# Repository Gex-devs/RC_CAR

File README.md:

# RC_CAR

ESP32 based RC Car using Xbox One Controller

## Components

## Software 

## Tools

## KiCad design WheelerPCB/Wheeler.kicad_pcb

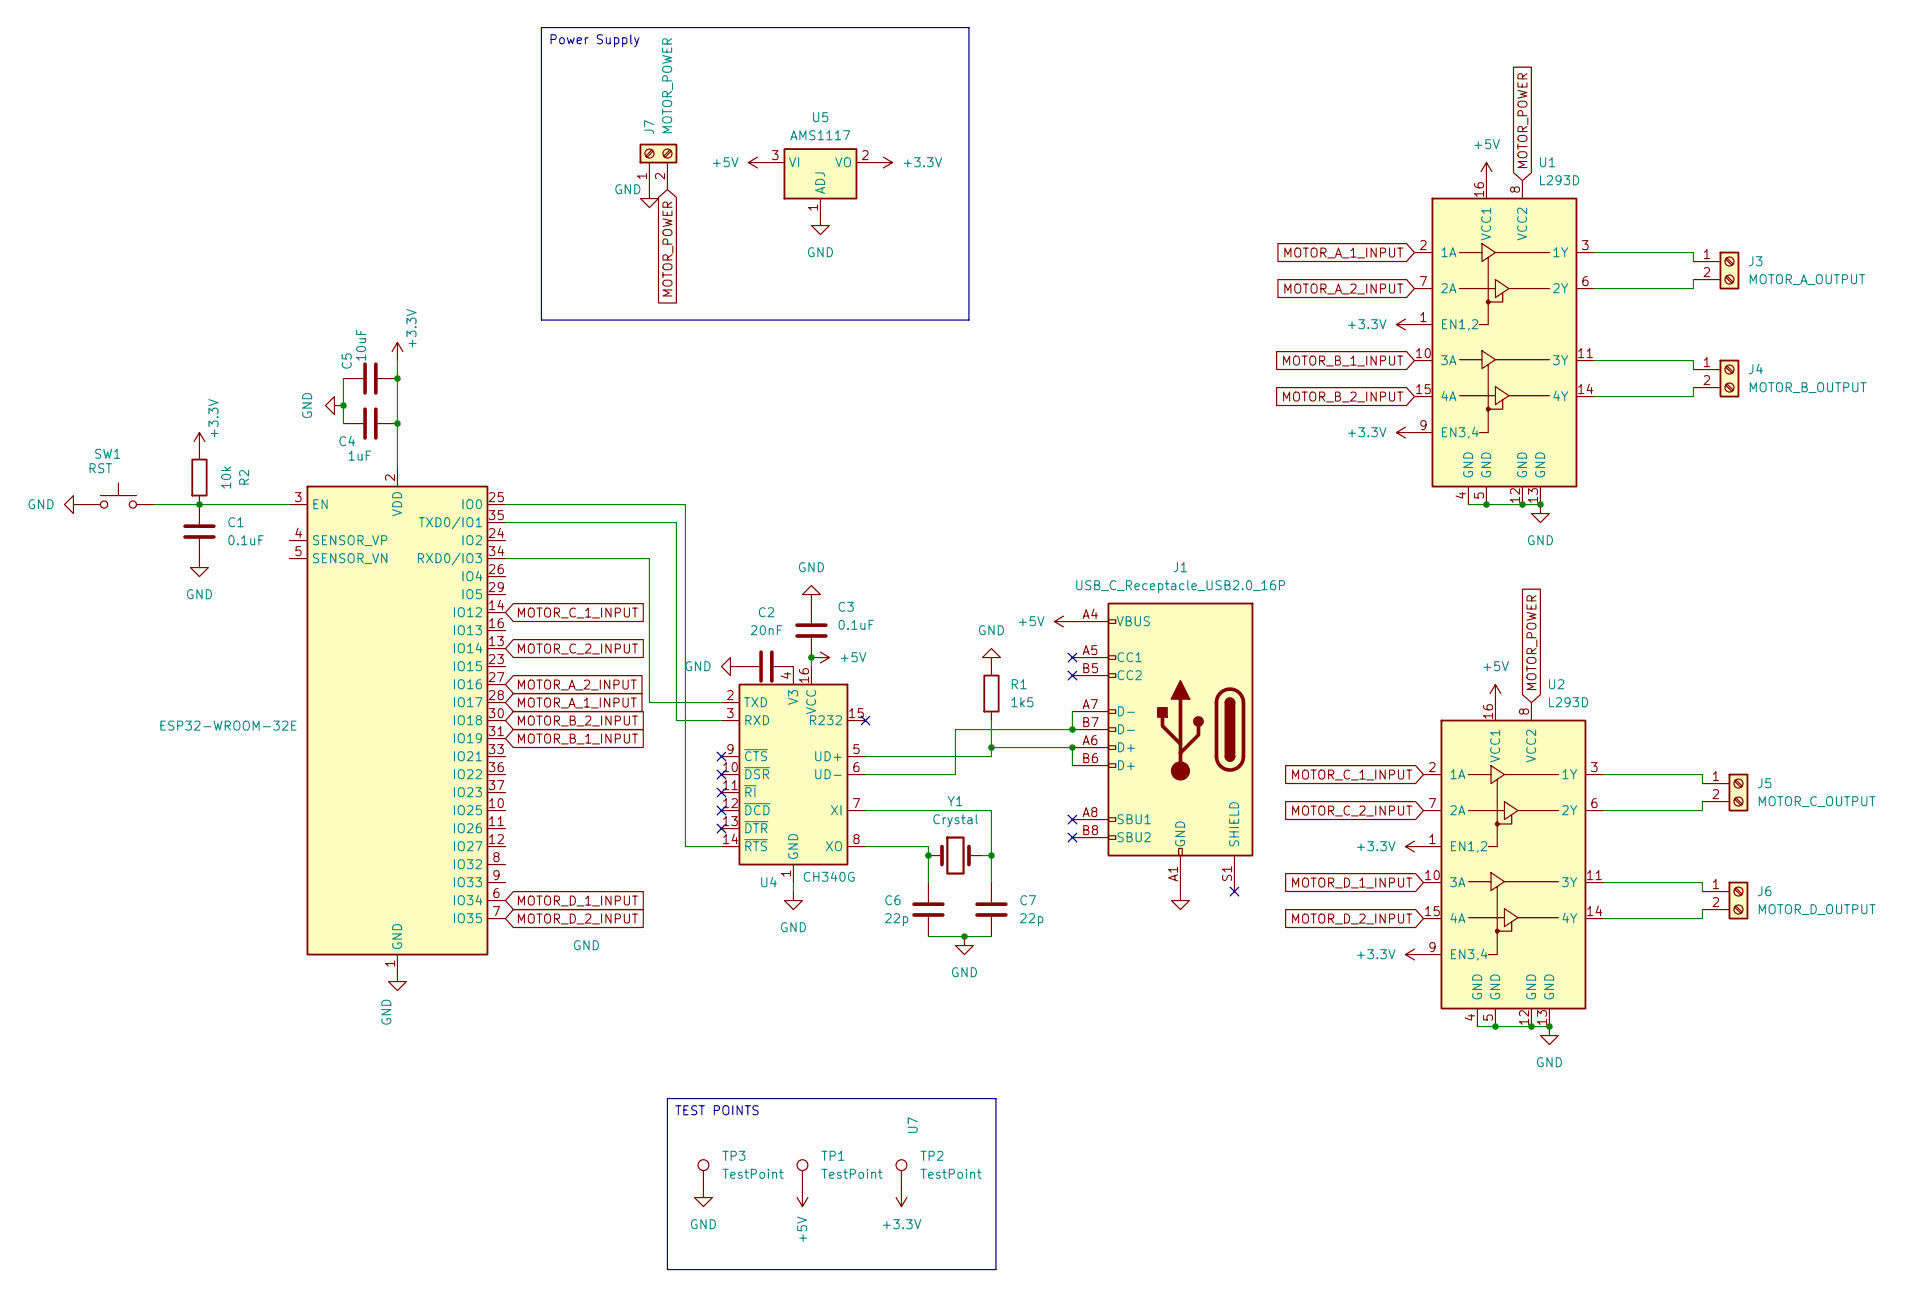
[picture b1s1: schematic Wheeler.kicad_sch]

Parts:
C1, C3: 0.1uF; C_0805_2012Metric
C2: 20nF; C_0805_2012Metric
C4: 1uF; C_0805_2012Metric
C5: 10uF; C_0805_2012Metric
C6, C7: 22p; C_0805_2012Metric
J1: USB_C_Receptacle_USB2.0_16P; USB_C_Receptacle_G-Switch_GT-USB-7010ASV
J3: MOTOR_A_OUTPUT; TerminalBlock_Xinya_XY308-2.54-2P_1x02_P2.54mm_Horizontal
J4: MOTOR_B_OUTPUT; TerminalBlock_Xinya_XY308-2.54-2P_1x02_P2.54mm_Horizontal
J5: MOTOR_C_OUTPUT; TerminalBlock_Xinya_XY308-2.54-2P_1x02_P2.54mm_Horizontal
J6: MOTOR_D_OUTPUT; TerminalBlock_Xinya_XY308-2.54-2P_1x02_P2.54mm_Horizontal
J7: MOTOR_POWER; TerminalBlock_Xinya_XY308-2.54-2P_1x02_P2.54mm_Horizontal
R1: 1k5; R_0805_2012Metric
R2: 10k; R_0805_2012Metric
SW1: RST; SW_PUSH_6mm_H4.3mm
TP1, TP2, TP3: TestPoint; Pin_D0.7mm_L6.5mm_W1.8mm_FlatFork
U1, U2: L293D; DIP-16_W7.62mm_Socket
U4: CH340G; SOIC-16_3.9x9.9mm_P1.27mm
U5: AMS1117; SOT-223-3_TabPin2
U7: ESP32-WROOM-32E; ESP32-WROOM-32D
Y1: Crystal; Crystal_HC49-4H_Vertical

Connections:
+3.3V: C4.1, C5.1, R2.1, TP2.1, U1.1 (EN1,2), U1.9 (EN3,4), U2.1 (EN1,2), U2.9 (EN3,4), U5.2 (VO), U7.2 (VDD)
+5V: C3.2, J1.A4 (VBUS), J1.A9 (VBUS), J1.B4 (VBUS), J1.B9 (VBUS), TP1.1, U1.16 (VCC1), U2.16 (VCC1), U4.16 (VCC), U5.3 (VI)
GND: C1.2, C2.2, C3.1, C4.2, C5.2, C6.2, C7.2, J1.A1 (GND), J1.A12 (GND), J1.B1 (GND), J1.B12 (GND), J7.1, R1.1, SW1.1, TP3.1, U1.4 (GND), U1.5 (GND), U1.12 (GND), U1.13 (GND), U2.4 (GND), U2.5 (GND), U2.12 (GND), U2.13 (GND), U4.1 (GND), U5.1 (ADJ), U7.1 (GND), U7.15 (GND), U7.38 (GND), U7.39 (GND)
MOTOR_A_1_INPUT: U1.2 (1A), U7.28 (IO17)
MOTOR_A_2_INPUT: U1.7 (2A), U7.27 (IO16)
MOTOR_B_1_INPUT: U1.10 (3A), U7.31 (IO19)
MOTOR_B_2_INPUT: U1.15 (4A), U7.30 (IO18)
MOTOR_C_1_INPUT: U2.2 (1A), U7.14 (IO12)
MOTOR_C_2_INPUT: U2.7 (2A), U7.13 (IO14)
MOTOR_D_1_INPUT: U2.10 (3A), U7.6 (IO34)
MOTOR_D_2_INPUT: U2.15 (4A), U7.7 (IO35)
MOTOR_POWER: J7.2, U1.8 (VCC2), U2.8 (VCC2)
unnamed: J3.1, U1.3 (1Y)
unnamed: J3.2, U1.6 (2Y)
unnamed: J4.1, U1.11 (3Y)
unnamed: J4.2, U1.14 (4Y)
unnamed: J5.1, U2.3 (1Y)
unnamed: J5.2, U2.6 (2Y)
unnamed: J6.1, U2.11 (3Y)
unnamed: J6.2, U2.14 (4Y)
unnamed: U4.3 (RXD), U7.35 (TXD0/IO1)
unnamed: U4.2 (TXD), U7.34 (RXD0/IO3)
unnamed: J1.A6 (D+), J1.B6 (D+), R1.2, U4.5 (UD+)
unnamed: J1.A7 (D-), J1.B7 (D-), U4.6 (UD-)
unnamed: C2.1, U4.4 (V3)
unnamed: C7.1, U4.7 (XI), Y1.2
unnamed: C6.1, U4.8 (XO), Y1.1
unnamed: U4.14 (~RTS), U7.25 (IO0)
unnamed: C1.1, R2.2, SW1.2, U7.3 (EN)

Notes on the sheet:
TEST POINTS
Power Supply

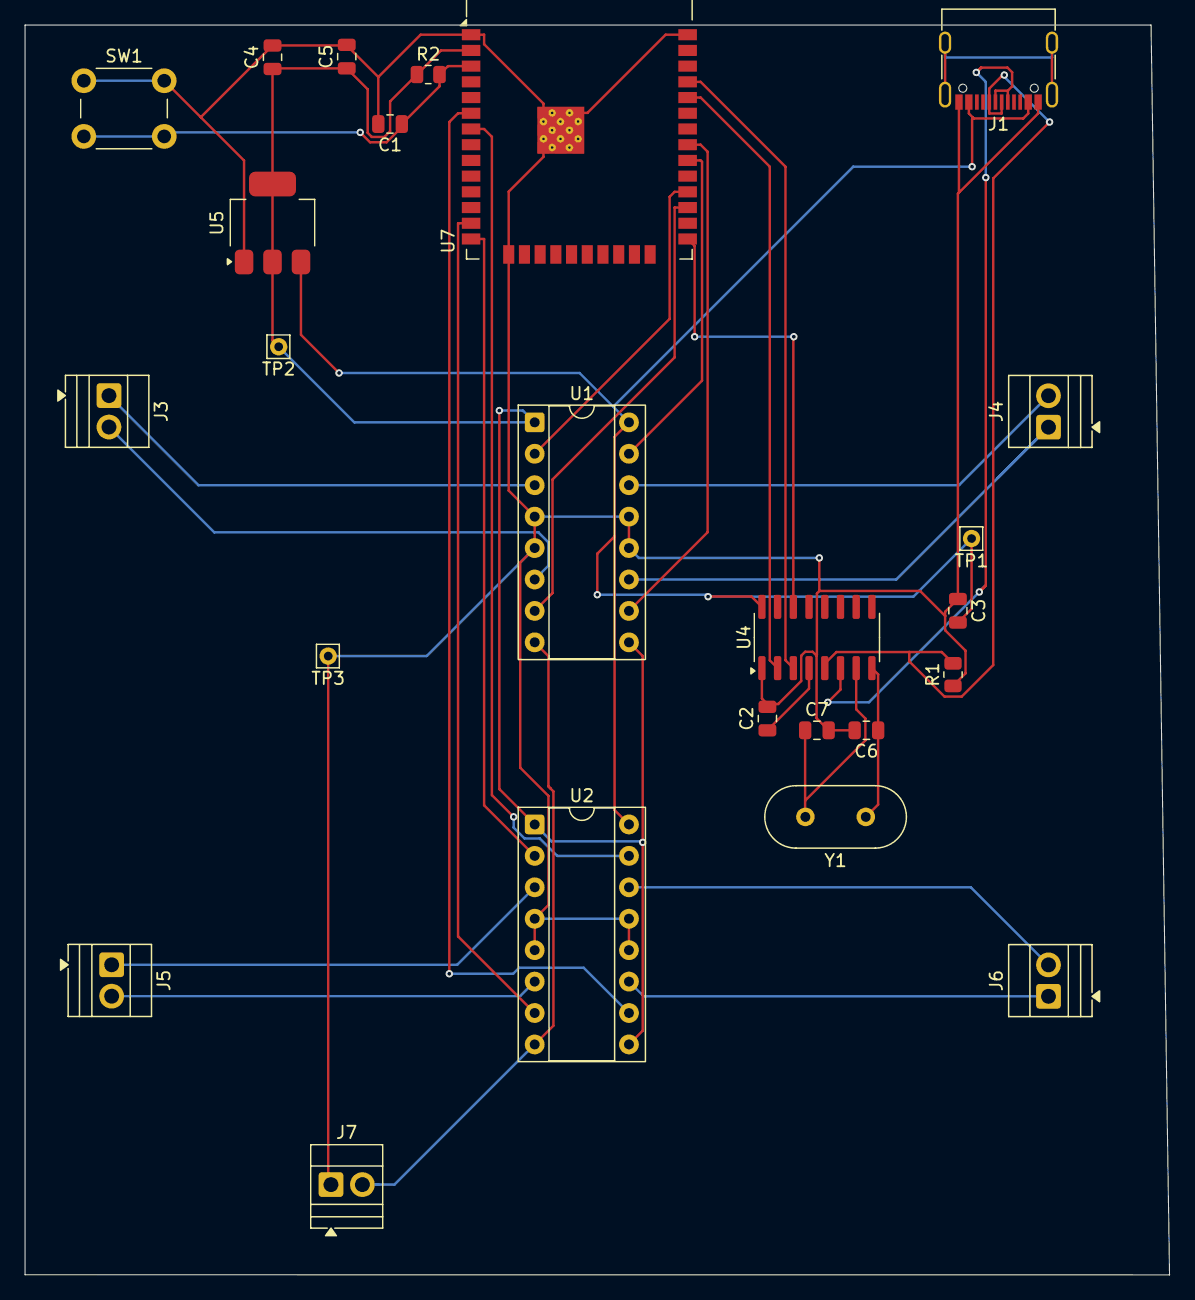
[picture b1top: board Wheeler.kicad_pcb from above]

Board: 2 copper layers, 92.5 x 101.0 mm, 25 parts (0 on the bottom side), 29 nets.

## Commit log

2023-04-15 organized
2023-04-18 adjusted configurations
2023-04-18 configured succ
2023-04-18 another succ
2023-04-23 added pics
2023-05-01 Working starter
2023-12-25 refractored env setup
2024-02-26 updated schematic
2024-02-28 updated eagle pcb schem
2024-03-19 update schematic
2024-03-20 updated schm
2024-05-02 Updated preview
2024-09-18 updated enviroment configuration for usbasp
2025-07-07 Updated Sch and moved from Eagle to Kicad
2025-08-11 Migrated to ESP32 and BLE
2025-08-13 Questionable Routing
2025-08-27 adjusted folder structure
2025-08-30 added dep
2025-08-30 added library
2025-08-30 removed modules
2025-08-30 added all required depencies and submodules. Compiles
2025-09-07 updated PCB Design and gitignore
2025-09-07 added workflow and updated ReadME(ish)
2025-09-07 workflow test
2025-09-07 who names their branch master???
2025-09-07 env is your best friend, workflow test 2
2025-09-07 Update schematic preview [skip ci]
